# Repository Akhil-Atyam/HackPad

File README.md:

# RGB Pad!
Hello guys, welcome to my README!
I have designed a 16 key macro pad with each key having an individually addressable LED, all according to the standards presented by the HackPad mission on Stardance (atleast hopefully).

## Key Features
* 16 Cherry MX Keys
* 16 Individually Adressable LEDS
* 1 0.91 Inch OLED Display

## Onshape link
Feel free to tour my cad!!!
ONSHAPE IS SUPER SLOW IF IT IS YOUR FIRST TIME LOADING IT. IT IS NOT AN ERROR, RATHER A THING ABOUT ONSHAPE ITSELF.
https://cad.onshape.com/documents/e1661e19116ea9c6de92e682/w/dd3611e2101036e24bcbff88/e/80689fdb4ae365a9a36d9549

## Design of PCB
Originally, I aimed to design a pcb with an encoder as well, but as complexity grew in wiring for charlieplexing, I pivoted.
)

Instead, I kept the same overall size but switched to a more simple matrix style for my design

## Design of Case
My case design was very simple, it is simply aimed to case my MacroPad, but I also wanted to be able to show off my RGB keys.
Therefore, I made my top case clear, but hopefully I can find someone that has PETG or PLA clear to print this for me.
I used onshape in order to create this as it is what I am most familiar with.

## Firmware 
For my firmware I used QMK to make this keyboard. It is what the guide recommended and so I followed that.
I added firmware for my LEDs, OLED, and mapped my Keyswitches.

## Overall

I had a lot of fun with this project, it taught me a lot about electronic design and was a major step up from my Blare project. Thank you stardance for this opportunity!

## BOM

BOM is in the CSV labelled as BOM.CSV
Unfortunately it is a bit large and I do not think it is appropriate to have it in the readme due to the size of the links.

## Photos

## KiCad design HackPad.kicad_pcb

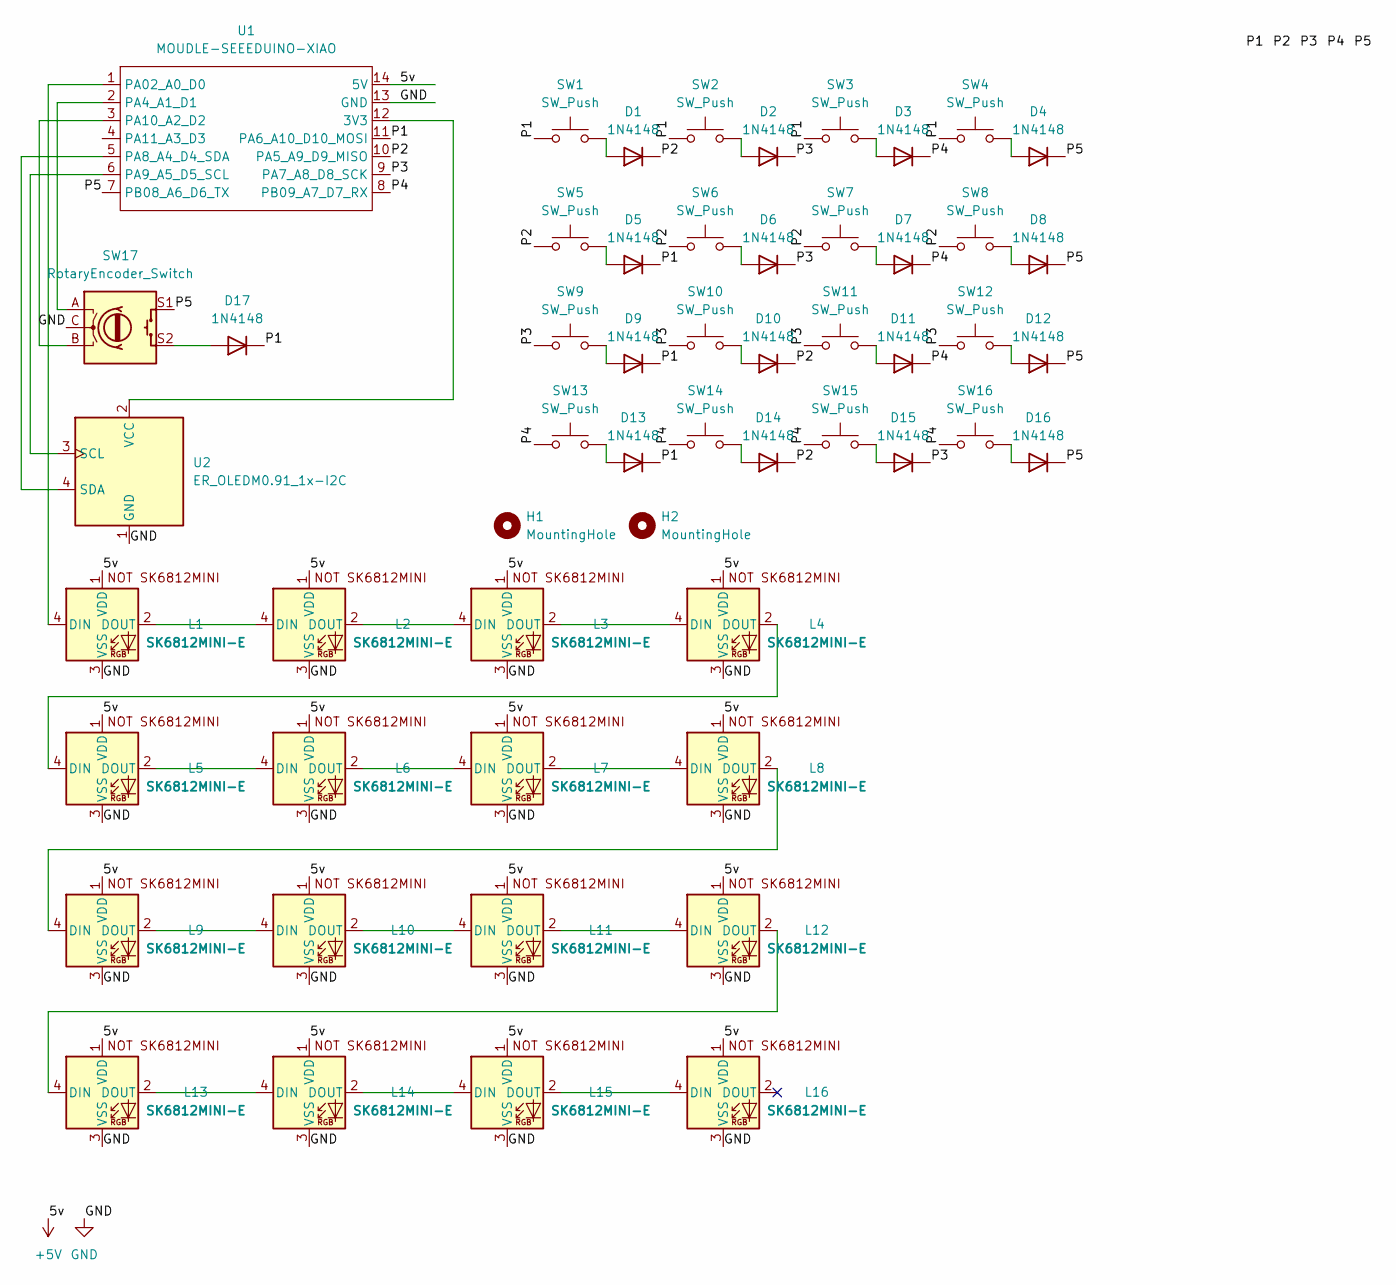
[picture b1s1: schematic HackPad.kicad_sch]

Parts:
D1, D2, D3, D4, D5, D6, D7, D8, D9, D10, D11, D12, D13, D14, D15, D16, D17: 1N4148; D_DO-35_SOD27_P7.62mm_Horizontal
H1, H2: MountingHole; MountingHole_3.2mm_M3
L1, L2, L3, L4, L5, L6, L7, L8, L9, L10, L11, L12, L13, L14, L15, L16: SK6812MINI-E; SK6812MINI-E_fixed
SW1, SW2, SW3, SW4, SW5, SW6, SW7, SW8, SW9, SW10, SW11, SW12, SW13, SW14, SW15, SW16: SW_Push; SW_Cherry_MX_1.00u_PCB
SW17: RotaryEncoder_Switch; RotaryEncoder_Alps_EC11E-Switch_Vertical_H20mm
U1: MOUDLE-SEEEDUINO-XIAO; XIAO-Generic-Hybrid-14P-2.54-21X17.8MM
U2: ER_OLEDM0.91_1x-I2C

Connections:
+5V: L1.1 (VDD), L2.1 (VDD), L3.1 (VDD), L4.1 (VDD), L5.1 (VDD), L6.1 (VDD), L7.1 (VDD), L8.1 (VDD), L9.1 (VDD), L10.1 (VDD), L11.1 (VDD), L12.1 (VDD), L13.1 (VDD), L14.1 (VDD), L15.1 (VDD), L16.1 (VDD), U1.14 (5V)
/P1: D5.1 (K), D9.1 (K), D13.1 (K), D17.1 (K), SW1.1, SW2.1, SW3.1, SW4.1, U1.11 (PA6_A10_D10_MOSI)
/P2: D1.1 (K), D10.1 (K), D14.1 (K), SW5.1, SW6.1, SW7.1, SW8.1, U1.10 (PA5_A9_D9_MISO)
/P3: D2.1 (K), D6.1 (K), D15.1 (K), SW9.1, SW10.1, SW11.1, SW12.1, U1.9 (PA7_A8_D8_SCK)
/P4: D3.1 (K), D7.1 (K), D11.1 (K), SW13.1, SW14.1, SW15.1, SW16.1, U1.8 (PB09_A7_D7_RX)
/P5: D4.1 (K), D8.1 (K), D12.1 (K), D16.1 (K), SW17.S1, U1.7 (PB08_A6_D6_TX)
GND: L1.3 (VSS), L2.3 (VSS), L3.3 (VSS), L4.3 (VSS), L5.3 (VSS), L6.3 (VSS), L7.3 (VSS), L8.3 (VSS), L9.3 (VSS), L10.3 (VSS), L11.3 (VSS), L12.3 (VSS), L13.3 (VSS), L14.3 (VSS), L15.3 (VSS), L16.3 (VSS), SW17.C, U1.13 (GND), U2.1 (GND)
unnamed: D1.2 (A), SW1.2
unnamed: D2.2 (A), SW2.2
unnamed: D3.2 (A), SW3.2
unnamed: D4.2 (A), SW4.2
unnamed: D5.2 (A), SW5.2
unnamed: D6.2 (A), SW6.2
unnamed: D7.2 (A), SW7.2
unnamed: D8.2 (A), SW8.2
unnamed: D9.2 (A), SW9.2
unnamed: D10.2 (A), SW10.2
unnamed: D11.2 (A), SW11.2
unnamed: D12.2 (A), SW12.2
unnamed: D13.2 (A), SW13.2
unnamed: D14.2 (A), SW14.2
unnamed: D15.2 (A), SW15.2
unnamed: D16.2 (A), SW16.2
unnamed: D17.2 (A), SW17.S2
unnamed: L1.4 (DIN), U1.1 (PA02_A0_D0)
unnamed: L1.2 (DOUT), L2.4 (DIN)
unnamed: L2.2 (DOUT), L3.4 (DIN)
unnamed: L3.2 (DOUT), L4.4 (DIN)
unnamed: L4.2 (DOUT), L5.4 (DIN)
unnamed: L5.2 (DOUT), L6.4 (DIN)
unnamed: L6.2 (DOUT), L7.4 (DIN)
unnamed: L7.2 (DOUT), L8.4 (DIN)
unnamed: L8.2 (DOUT), L9.4 (DIN)
unnamed: L9.2 (DOUT), L10.4 (DIN)
unnamed: L10.2 (DOUT), L11.4 (DIN)
unnamed: L11.2 (DOUT), L12.4 (DIN)
unnamed: L12.2 (DOUT), L13.4 (DIN)
unnamed: L13.2 (DOUT), L14.4 (DIN)
unnamed: L14.2 (DOUT), L15.4 (DIN)
unnamed: L15.2 (DOUT), L16.4 (DIN)
unnamed: U1.12 (3V3), U2.2 (VCC)
unnamed: SW17.A, U1.2 (PA4_A1_D1)
unnamed: U1.5 (PA8_A4_D4_SDA), U2.4 (SDA)
unnamed: U1.6 (PA9_A5_D5_SCL), U2.3 (SCL)
unnamed: SW17.B, U1.3 (PA10_A2_D2)

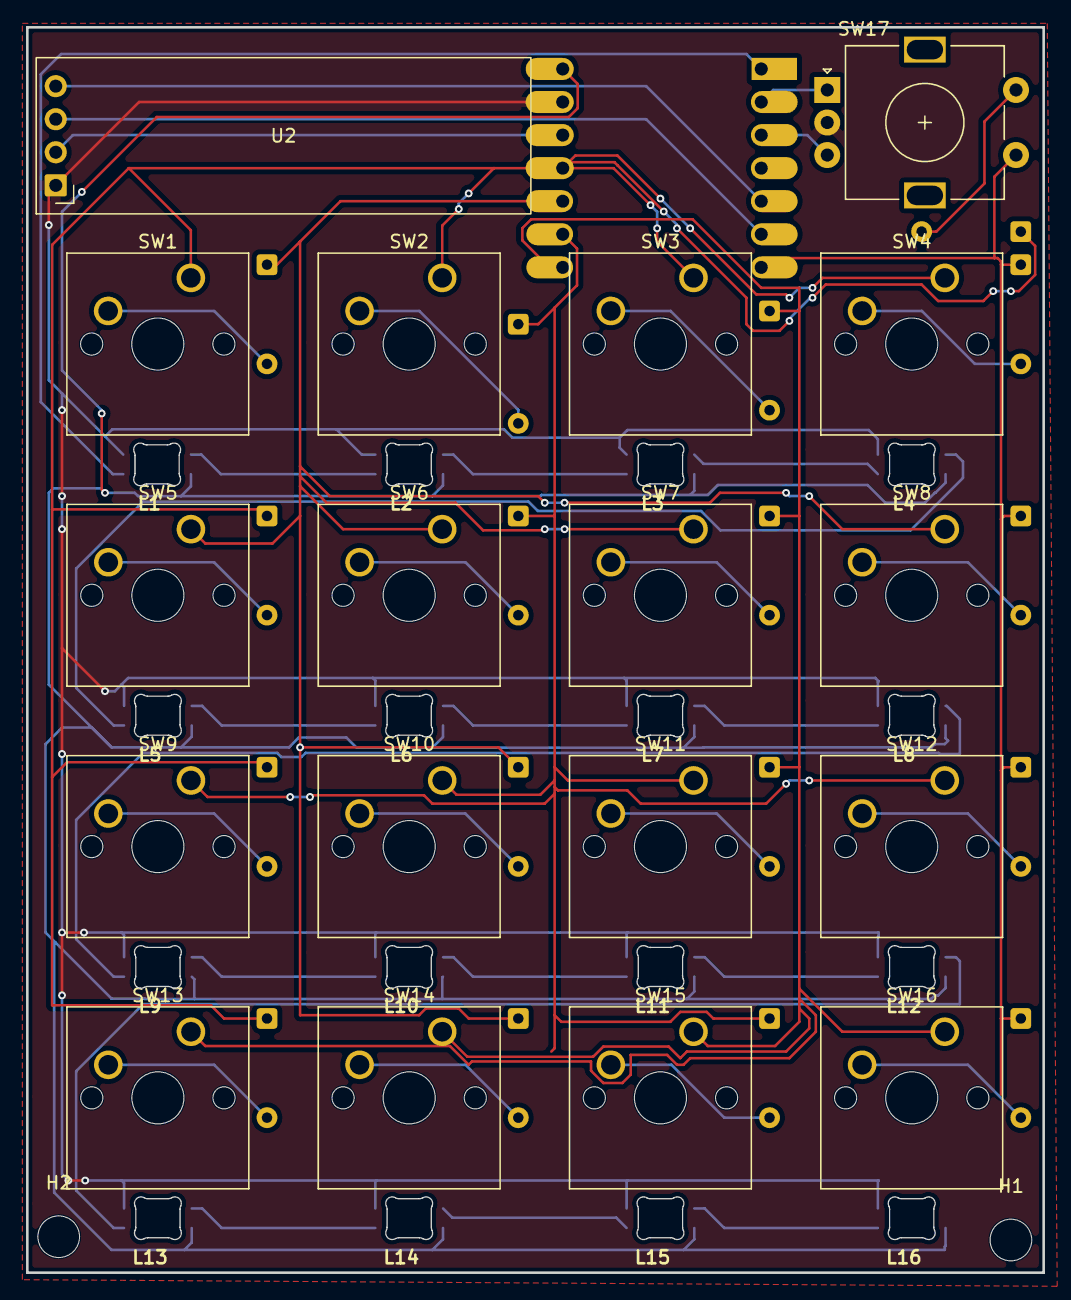
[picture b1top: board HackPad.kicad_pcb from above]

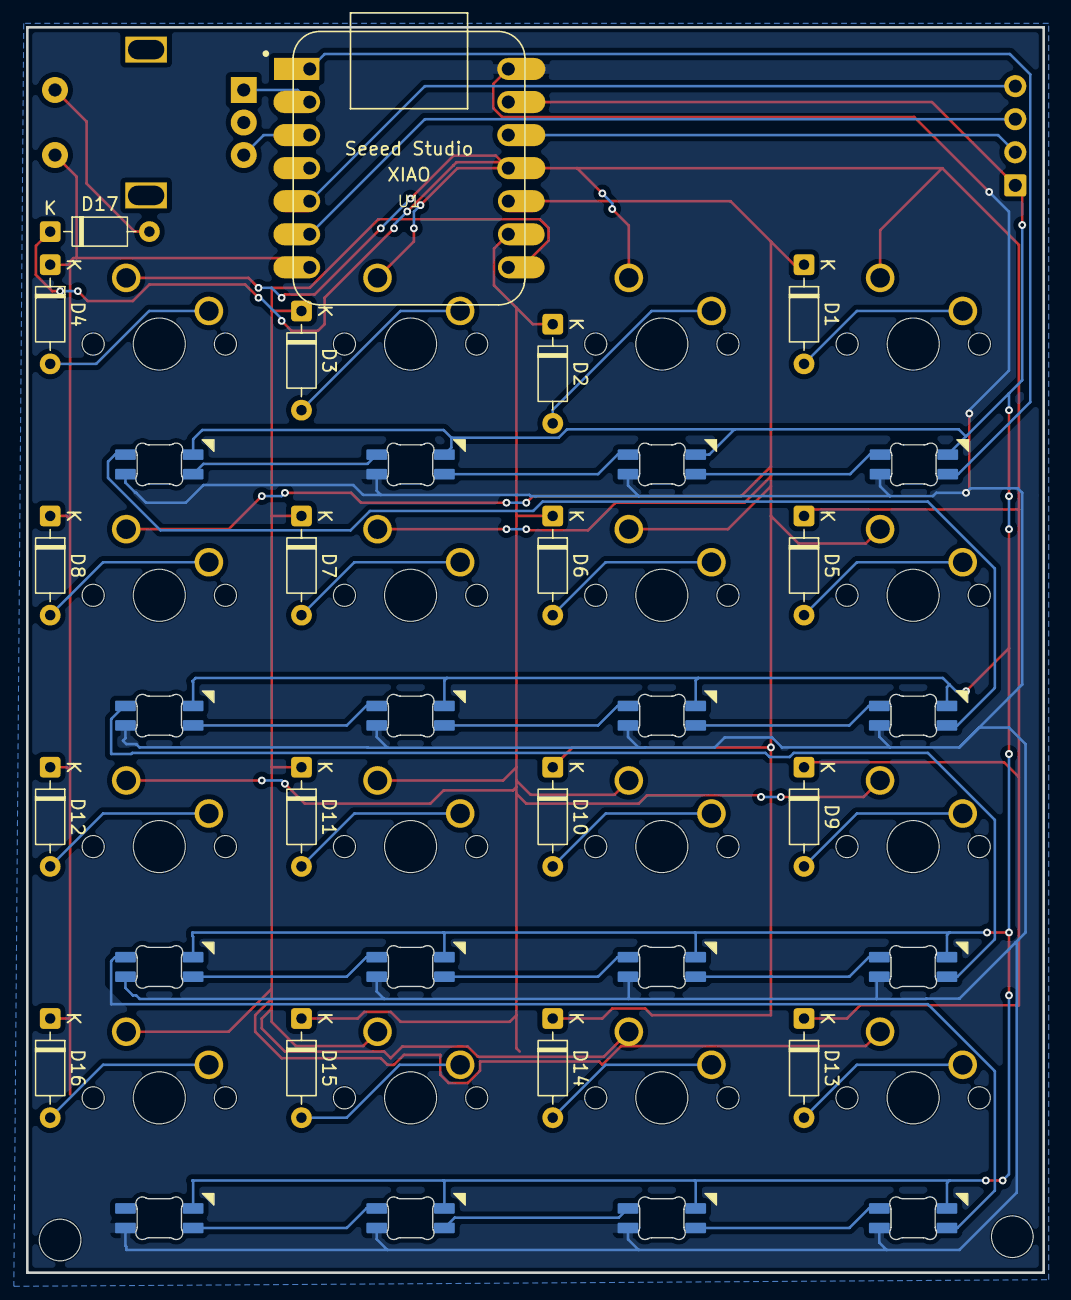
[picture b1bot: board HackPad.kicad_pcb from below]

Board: 2 copper layers, 78.1 x 95.7 mm, 54 parts (18 on the bottom side), 45 nets.
